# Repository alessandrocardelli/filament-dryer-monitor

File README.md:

# Filament Dryer Monitor

ESP32 controller for eSUN eBOX Lite. **`main` is the non-heating SAFE BRING-UP reference; its heater output remains locked OFF.**

Current development continues exclusively on [`experiment/step10-heater-diagnostics-air25-2026-10-28`](https://github.com/alessandrocardelli/filament-dryer-monitor/blob/experiment/step10-heater-diagnostics-air25-2026-10-28/docs/PROJECT_STATE.md), [PR #18 DRAFT](https://github.com/alessandrocardelli/filament-dryer-monitor/pull/18). Read that branch's [PROJECT_STATE](https://github.com/alessandrocardelli/filament-dryer-monitor/blob/experiment/step10-heater-diagnostics-air25-2026-10-28/docs/PROJECT_STATE.md) for current source, physical evidence, installed-image uncertainty and unresolved qualification, and [TODO](https://github.com/alessandrocardelli/filament-dryer-monitor/blob/experiment/step10-heater-diagnostics-air25-2026-10-28/docs/TODO.md) for its priority. The experimental branch is HEATER-capable and is not an autonomous-use approval. No experimental code is integrated here.

Main's local menu, cycle timer, settings, branding and recorded peripheral bring-up remain available. Read [AGENTS](AGENTS.md), [main state](docs/PROJECT_STATE.md), [decisions](docs/DECISIONS.md), [firmware](firmware/README.md), [assembly](docs/ASSEMBLY.md) and [buck design](docs/BUCK_L7987L_DESIGN.md).

The former detailed README is preserved in the [historical snapshot](https://github.com/alessandrocardelli/filament-dryer-monitor/blob/5a805d7ed5a74a13dc89a412c7981aae5ce8958b/README.md). Its N8580 upload/next-test instructions are superseded by the active branch's state; do not execute them as a current plan. D020 belongs to a deliberate future hardware revision; installed series TCO105 remains unchanged (D029).

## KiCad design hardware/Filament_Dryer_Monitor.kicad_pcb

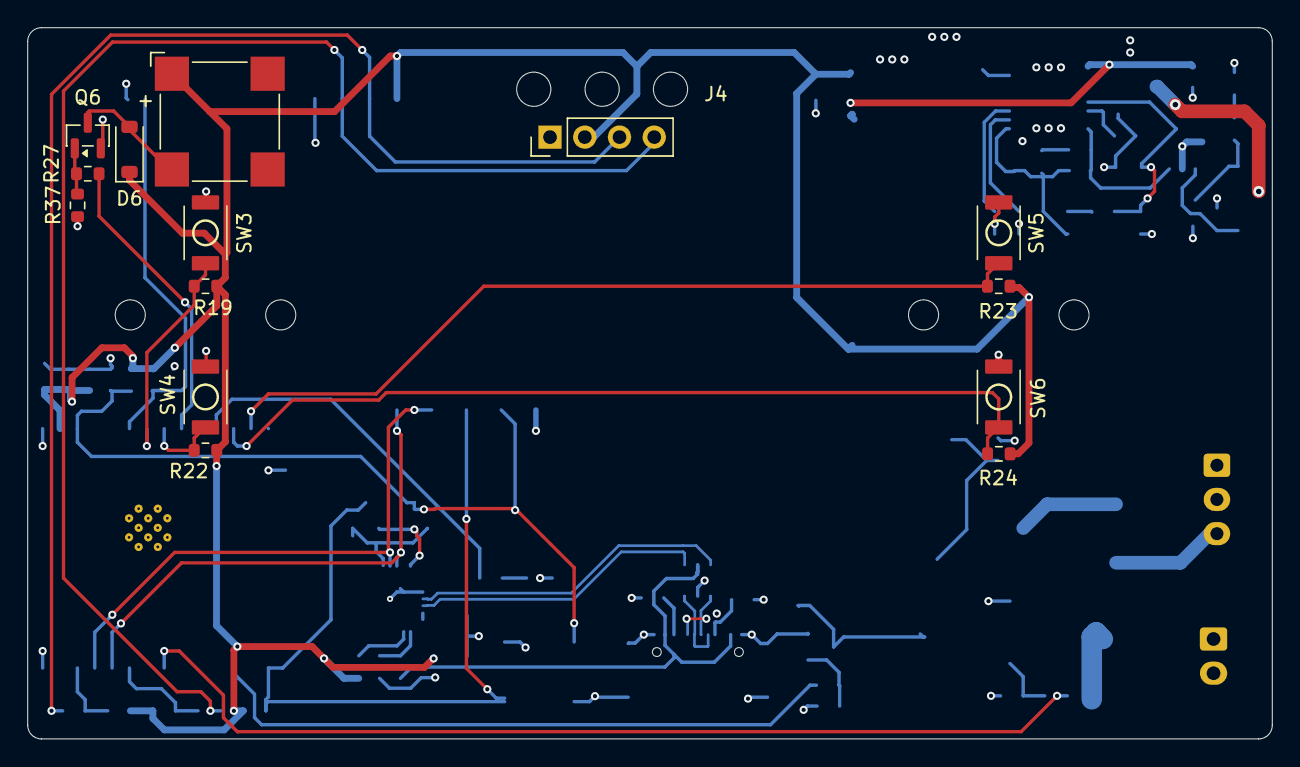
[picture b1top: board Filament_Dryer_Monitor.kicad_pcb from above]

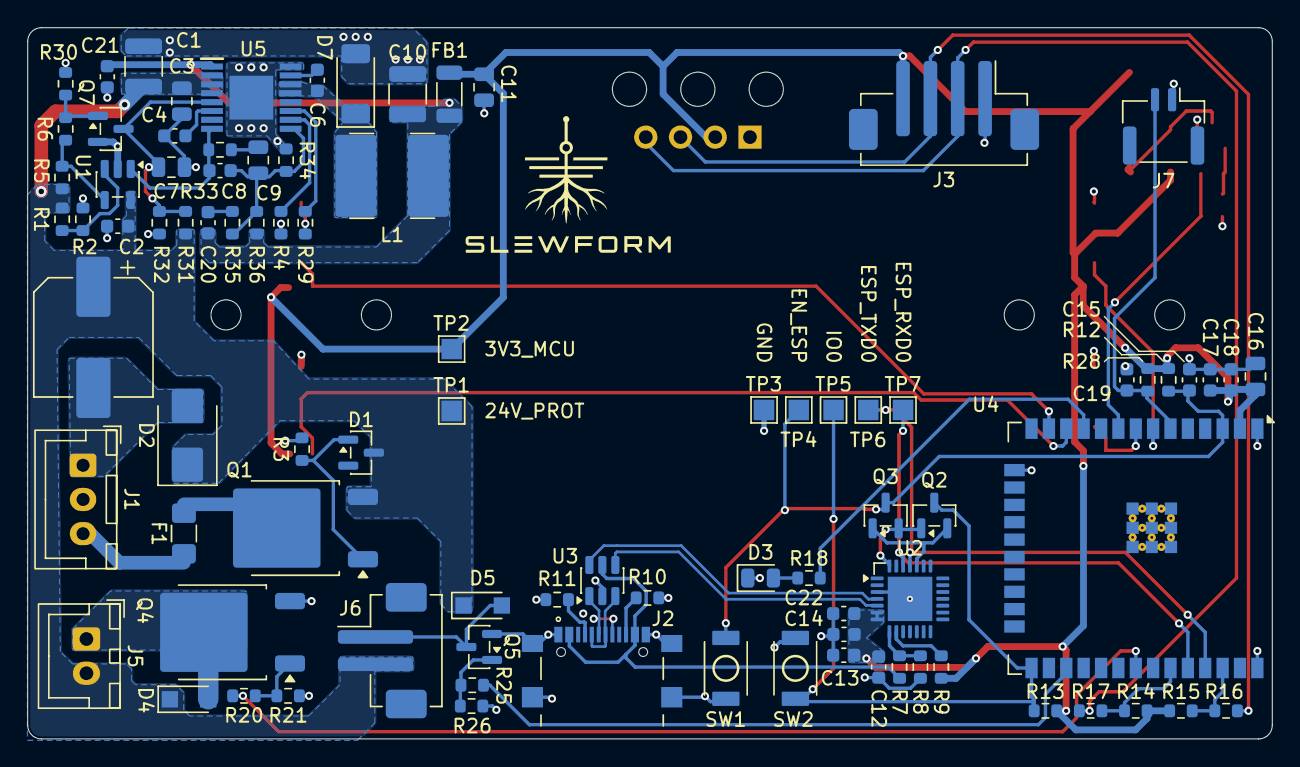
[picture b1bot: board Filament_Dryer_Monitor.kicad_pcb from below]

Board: 4 copper layers, 91.0 x 52.0 mm, 102 parts (88 on the bottom side), 55 nets.

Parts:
BZ1: LD-BZEL-T67-0808; BUZ_Loudity_SMT67_8.5x8.5
C1: 10u; C_1210_3225Metric
C2, C6, C13, C14, C18, C19: 100n; C_0603_1608Metric
C3: 1u; C_0805_2012Metric
C4: 33n; C_0603_1608Metric
C5: 100u; CP_Panasonic_F_8x10.2
C7: 330n; C_0805_2012Metric
C8: 39p; C_0603_1608Metric
C9: 18n; C_0805_2012Metric
C10: 47u; C_1210_3225Metric
C11: 22u; C_0805_2012Metric
C12: 4u7; C_0603_1608Metric
C15, C17, C21, C22: 1u; C_0603_1608Metric
C16: 10u; C_0805_2012Metric
C20: 560p; C_0603_1608Metric
D1: BZX84C15-7-F; SOT-23
D2: SMBJ28A; D_SMB
D3: LED_Small; LED_0805_2012Metric
D4, D5: PMEG6020ER; Nexperia_CFP3_SOD-123W
D6: 1N4148W; D_SOD-123
D7: PMEG6030EP; D_SOD-128
F1: T3A/63V; Fuse_1206_3216Metric_Pad1.42x1.75mm_HandSolder
FB1: BLM31KN601SH1L; L_1206_3216Metric
J1: DC Connector; JST_XH_B3B-XH-A_1x03_P2.50mm_Vertical
J2: USB_C_Receptacle_USB2.0_16P; USB_C_GCT_USB4216-03-A
J3: Sensor; JST_PH_B4B-PH-SM4-TB_1x04-1MP_P2.00mm_Vertical
J4: Display; Oled 1.54 Inch SSD1309 TZT
J5: Heater Connector; JST_XH_B2B-XH-A_1x02_P2.50mm_Vertical
J6: Fan Connector; JST_PH_B2B-PH-SM4-TB_1x02-1MP_P2.00mm_Vertical
J7: NTC Connector; JST_GH_BM02B-GHS-TBT_1x02-1MP_P1.25mm_Vertical
L1: 15u; L_Bourns_SRN6045
Q1: NTD20P06LT4G; TO-252-2
Q2, Q3, Q6, Q7: MMBT3904; SOT-23
Q4: IRLR3636TRPBF; TO-252-2
Q5: IRLML2060TRPBF; SOT-23
R1: 270k; R_0603_1608Metric
R2: 22k; R_0603_1608Metric
R3, R5, R6, R21, R26, R31, R37: 100k; R_0603_1608Metric
R4, R28, R30: 47k; R_0603_1608Metric
R7: 22k1; R_0603_1608Metric
R8, R29: 47k5; R_0603_1608Metric
R9: 1k; R_0603_1608Metric
R10, R11: 5k1; R_0603_1608Metric
R12, R13, R14, R15, R19, R22, R23, R24: 10k; R_0603_1608Metric
R16, R17: 33; R_0603_1608Metric
R18: 330; R_0603_1608Metric
R20, R25: 100; R_0603_1608Metric
R27: 470; R_0603_1608Metric
R32: 15k; R_0603_1608Metric
R33, R34: 16k; R_0603_1608Metric
R35: 1k13; R_0603_1608Metric
R36: 49k9; R_0603_1608Metric
SW1, SW2, SW3, SW4, SW5, SW6: SW_GCT_SWT0110
TP1: 24V_PROT; TestPoint_Pad_1.5x1.5mm
TP2: 3V3_MCU; TestPoint_Pad_1.5x1.5mm
TP3: GND; TestPoint_Pad_1.5x1.5mm
TP4: EN_ESP; TestPoint_Pad_1.5x1.5mm
TP5: IO0; TestPoint_Pad_1.5x1.5mm
TP6: ESP_TXD0; TestPoint_Pad_1.5x1.5mm
TP7: ESP_RXD0; TestPoint_Pad_1.5x1.5mm
U1: TLV1701; SOT-23-5
U2: CP2102-GM; CP2102_GM_QFN28_5x5_P0.5_EP3.25
U3: AKS1201; SOT-23-6
U4: ESP32-WROOM-32E-N4; ESP32-WROOM-32E
U5: L7987L; SOP65P640X120-17N

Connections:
3V3_MCU: BZ1.1 (+), C11.1, C12.1, C13.1, C14.1, C16.1, C17.1, C18.1, C22.1, D6.1 (K), FB1.2, J3.4, J4.2, R9.1, R12.1, R13.1, R14.1, R15.1, R19.2, R22.2, R23.2, R24.2, R28.2, TP2.1 (1_1), U2.6 (VDD), U2.7 (REGIN), U4.2 (VDD)
24V_PROT: C1.1, C2.1, C3.1, C5.1, D1.3 (K), D2.1 (K), D4.1 (K), D5.1 (K), J5.2, J6.2, Q1.3 (S), R1.1, R5.1, R31.1, TP1.1 (1_1), U1.5 (V+), U5.2 (VIN_1), U5.3 (VIN_2), U5.4 (VCC)
/IO_Power/HEATER_SW: D4.2 (A), J5.1, Q4.2 (D)
/MCU/ESP_RXD0: TP7.1 (1_1), U2.26 (TXD), U4.34 (RXD0/IO3)
/MCU/ESP_TXD0: TP6.1 (1_1), U2.25 (RXD), U4.35 (TXD0/IO1)
/MCU/LED_DRV: R18.2, U4.11 (IO26)
/MCU/SCL: R15.2, R16.1, U4.36 (IO22)
/MCU/SDA: R14.2, R17.1, U4.33 (IO21)
/MCU/USB_CONN_D+: J2.A6 (D+), J2.B6 (D+), U3.1 (I/O1)
/MCU/USB_CONN_D-: J2.A7 (D-), J2.B7 (D-), U3.3 (I/O2)
/MCU/USB_D+: U2.4 (D+), U3.6 (I/O1)
/MCU/USB_D-: U2.5 (D-), U3.4 (I/O2)
/MCU/USB_VBUS: J2.A4 (VBUS), J2.A9 (VBUS), J2.B4 (VBUS), J2.B9 (VBUS), R7.1, U3.5 (VBUS)
/Power/3V3_BUCK: C10.1, C20.2, C21.1, FB1.1, L1.2, R36.2, U5.1 (VBIAS)
/Power/COMP: C8.1, R33.1, U1.1 (+), U5.8 (COMP)
/Power/EN: C7.1, Q7.3 (C), R31.2, R32.1, U5.5 (EN)
/Power/FUSE_OUT: F1.2, Q1.2 (D)
/Power/GATE_Q1: D1.1 (A), Q1.1 (G), R3.1
/Power/JACK_24V_RAW: F1.1, J1.3
/Power/VREF_FAULT: R1.2, R2.1, U1.3 (-)
BTN_DOWN: R24.1, SW6.2, U4.12 (IO27)
BTN_M: R22.1, SW4.2, U4.8 (IO32)
BTN_ONOFF: R19.1, SW3.2, U4.7 (IO35)
BTN_UP: R23.1, SW5.2, U4.13 (IO14)
BUZ_DRV: R27.2, U4.9 (IO33)
FAN_PWM: R25.2, U4.27 (IO16)
GND: C1.2, C2.2, C3.2, C4.2, C5.2, C7.2, C10.2, C11.2, C12.2, C13.2, C14.2, C15.2, C16.2, C17.2, C18.2, C19.2, C21.2, C22.2, D2.2 (A), D3.1 (K), D7.2 (A), J1.1, J2.A1 (GND), J2.A12 (GND), J2.B1 (GND), J2.B12 (GND), J2.SH (SHIELD), J3.1, J4.1, J7.1, Q4.3 (S), Q5.2 (S), Q6.2 (E), Q7.2 (E), R2.2, R3.2, R4.2, R8.2, R10.2, R11.2, R21.1, R26.1, R29.2, R30.2, R32.2, R34.1, R37.1, SW1.1, SW2.1, SW3.1, SW4.1, SW5.1, SW6.1, TP3.1 (1_1), U1.2 (V-), U2.3 (GND), U2.29 (GND), U3.2 (GND), U4.1 (GND), U4.15 (GND), U4.38 (GND), U4.39 (GND), U5.16 (GND), U5.17 (SGND)
HEATER_PWM: R20.2, U4.31 (IO19)
NTC: C19.1, J7.2, R28.1, U4.6 (IO34)
unnamed: C9.1, R33.2
unnamed: C20.1, R35.2
unnamed: D3.2 (A), R18.1
unnamed: D5.2 (A), J6.1, Q5.3 (D)
unnamed: BZ1.2, D6.2 (A), Q6.3 (C)
unnamed: C6.2, D7.1 (K), L1.1, U5.13 (LX_1), U5.14 (LX_2)
unnamed: J2.A5 (CC1), R11.1
unnamed: J2.B5 (CC2), R10.1
unnamed: J3.2, J4.4, R17.2
unnamed: J3.3, J4.3, R16.2
unnamed: Q2.1 (B), Q3.2 (E), U2.28 (~DTR)
unnamed: Q2.3 (C), R13.2, SW2.2, TP5.1 (1_1), U4.25 (IO0)
unnamed: Q2.2 (E), Q3.1 (B), U2.24 (~RTS)
unnamed: C15.1, Q3.3 (C), R12.2, SW1.2, TP4.1 (1_1), U4.3 (EN)
unnamed: Q4.1 (G), R20.1, R21.2
unnamed: Q5.1 (G), R25.1, R26.2
unnamed: Q6.1 (B), R27.1, R37.2
unnamed: Q7.1 (B), R6.2, R30.1
unnamed: R5.2, R6.1, U1.4
unnamed: R7.2, R8.1, U2.8 (VBUS)
unnamed: R9.2, U2.9 (~RST)
unnamed: C6.1, U5.15 (BOOT)
unnamed: C8.2, C9.2, R34.2, R35.1, R36.1, U5.9 (FB)
unnamed: R4.1, U5.10 (FSW)
unnamed: R29.1, U5.11 (ILIM)
unnamed: C4.1, U5.6 (SS)

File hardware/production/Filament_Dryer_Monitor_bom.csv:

Designator,Footprint,Quantity,Value,LCSC Part #
BZ1,BUZ_Loudity_SMT67_8.5x8.5,1,LD-BZEL-T67-0808,LD-BZEL-T67-0808
C1,1210,1,10u,GRM32EC72A106KE05L
C10,1210,1,47u,LMK325B7476KM-PR
C11,0805,1,22u,C45783
C12,0603,1,4u7,C19666
"C13, C14, C18, C19",0603,4,100n,C14663
"C15, C17",0603,2,1u,C5199872
C16,0805,1,10u,C15850
"C2, C6",0603,2,100n,CC0603KRX7R9BB104
C20,0603,1,560p,06035A561JAT2A
"C21, C22",0603,2,1u,GCM188R71E105KA64J
C3,0805,1,1u,GRJ21BC72A105KE11L
C4,0603,1,33n,GCM188R71H333KA55D
C5,CP_Panasonic_F_8x10.2,1,100u,EEEFK1H101P
C7,0805,1,330n,GRM219R71H334KA88D
C8,0603,1,39p,C0603C390J5GACTU
C9,0805,1,18n,GRM21B5C1H183JA01L
D1,SOT-23,1,BZX84C15-7-F,C500789
D2,D_SMB,1,SMBJ28A,C96335
D3,0805,1,LED_Small,C5569446
"D4, D5",Nexperia_CFP3_SOD-123W,2,PMEG6020ER,C98663
D6,D_SOD-123,1,1N4148W,C81598
D7,D_SOD-128,1,PMEG6030EP,PMEG6030EP.115
F1,1206,1,T3A/63V,C354897
FB1,1206,1,BLM31KN601SH1L,C357023 
J1,JST_XH_B3B-XH-A_1x03_P2.50mm_Vertical,1,DC Connector,B3B-XH-A (LF)(SN)
J2,USB_C_GCT_USB4216-03-A,1,USB_C_Receptacle_USB2.0_16P,USB4216-03-A
J3,JST_PH_B4B-PH-SM4-TB_1x04-1MP_P2.00mm_Vertical,1,Sensor,B4B-PH-SM4-TB (LF)(SN)
J5,JST_XH_B2B-XH-A_1x02_P2.50mm_Vertical,1,Heater Connector,Kit HALJIA XH-compatible 2P
J6,JST_PH_B2B-PH-SM4-TB_1x02-1MP_P2.00mm_Vertical,1,Fan Connector,B2B-PH-SM4-TB (LF)(SN)
J7,JST_GH_BM02B-GHS-TBT_1x02-1MP_P1.25mm_Vertical,1,NTC Connector,C161690
L1,L_Bourns_SRN6045,1,15u,SRN6045-150M
Q1,TO-252-2,1,NTD20P06LT4G,C93034
"Q2, Q3, Q6",SOT-23,3,MMBT3904,C94514
Q4,TO-252-2,1,IRLR3636TRPBF,C67279
Q5,SOT-23,1,IRLML2060TRPBF,C75882
Q7,SOT-23,1,MMBT3904,MMBT3904
R1,0603,1,270k,RC0603FR-07270KL
"R10, R11",0603,2,5k1,C23186
"R12, R13, R14, R15, R19, R22, R23, R24",0603,8,10k,C25804
"R16, R17",0603,2,33,C23140
R18,0603,1,330,C23138
R2,0603,1,22k,RC0603FR-0722KL
"R20, R25",0603,2,100,C22775
"R21, R26, R3",0603,3,100k,C25803
R27,0603,1,470,C23179
R28,0603,1,47k,C25819
R29,0603,1,47k5,RC0603FR-0747K5L
"R30, R4",0603,2,47k,RC0603FR-0747KL
"R31, R37, R5, R6",0603,4,100k,RC0603FR-07100KL
R32,0603,1,15k,RC0603FR-0715KL
"R33, R34",0603,2,16k,RC0603FR-0716KL
R35,0603,1,1k13,ERA3AEB1131V
R36,0603,1,49k9,RC0603FR-0749K9L
R7,0603,1,22k1,C25961
R8,0603,1,47k5,C23061
R9,0603,1,1k,C21190
"SW1, SW2, SW3, SW4, SW5, SW6",SW_GCT_SWT0110,6,~,SWT0110-020010SSA
U1,SOT-23-5,1,TLV1701,TLV1701AIDBVR
U2,CP2102_GM_QFN28_5x5_P0.5_EP3.25,1,CP2102-GM,CP2102-GM
U3,SOT-23-6,1,AKS1201,C7519
U4,ESP32-WROOM-32E,1,ESP32-WROOM-32E-N4,ESP32-WROOM-32E-N4
U5,SOP65P640X120-17N,1,L7987L,L7987L
